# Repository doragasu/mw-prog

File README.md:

# WARNING: THIS PROJECT HAS MOVED

You can find the most recent version at the [mw-prog GitLab project page](https://gitlab.com/doragasu/mw-prog). This repository will be kept as is, and will not be updated anymore.

# mw-prog
MegaWiFi Programmer

This programmer is for the MegaWiFi project. It can write SEGA Genesis/Megadrive ROM files to MegaWiFi cartridges (up to 32 Mbit). It can also upload firmware blobs to the WiFi module inside MegaWiFi cartridges. To do so, you will need:

- Programmer bootloader: https://github.com/doragasu/mw-mdma-bl
- Programmer firmware: https://github.com/doragasu/mw-mdma-fw
- Programmer command-line interface: https://github.com/doragasu/mw-mdma-cli

And of course a both a MegaWiFi programmer and the target MegaWiFi cartridge.

This project was initially created for 1985alternativo, but to this day, no brave soul has dared to make an online game using this cart. Are you brave enough to try?

## License
mw-prog is licensed under the [CERN OHL 1.2](http://www.ohwr.org/licenses/cern-ohl/v1.2) license. You are free to study, distribute and make modifications to the Documentation, under the aforementioned license terms. You are also free to make cartridges derived from the Documentation for non-commercial purposes. If you want to make a commercial Product using this Documentation, please contact me to obtain a licence.

## About CAD files
Electronic CAD design files are for KiCAD Open Source electronics design suite. Please install latest version along with KiCAD libraries to open the project. When opening schematic, KiCAD will most likely complain about missing library "doragasu". Despite this warning, the schematic should load nicely (using the cached libraries). To avoid this message, install [the missing library](https://github.com/doragasu/doragasu-kicad-lib) and make sure to configure it in the schematic editor.

The files under `gerber` directory are for PCB fabrication. Send them to your favorite PCB fab house.

Files under `enclosure` directory are for the design and fabrication of the PCB enclosure. You can 3D-print the OBJ files to have a not specially pretty but functional enclosure for the programmer. If you want to edit the design files, you will need FreeCAD.

Enjoy!

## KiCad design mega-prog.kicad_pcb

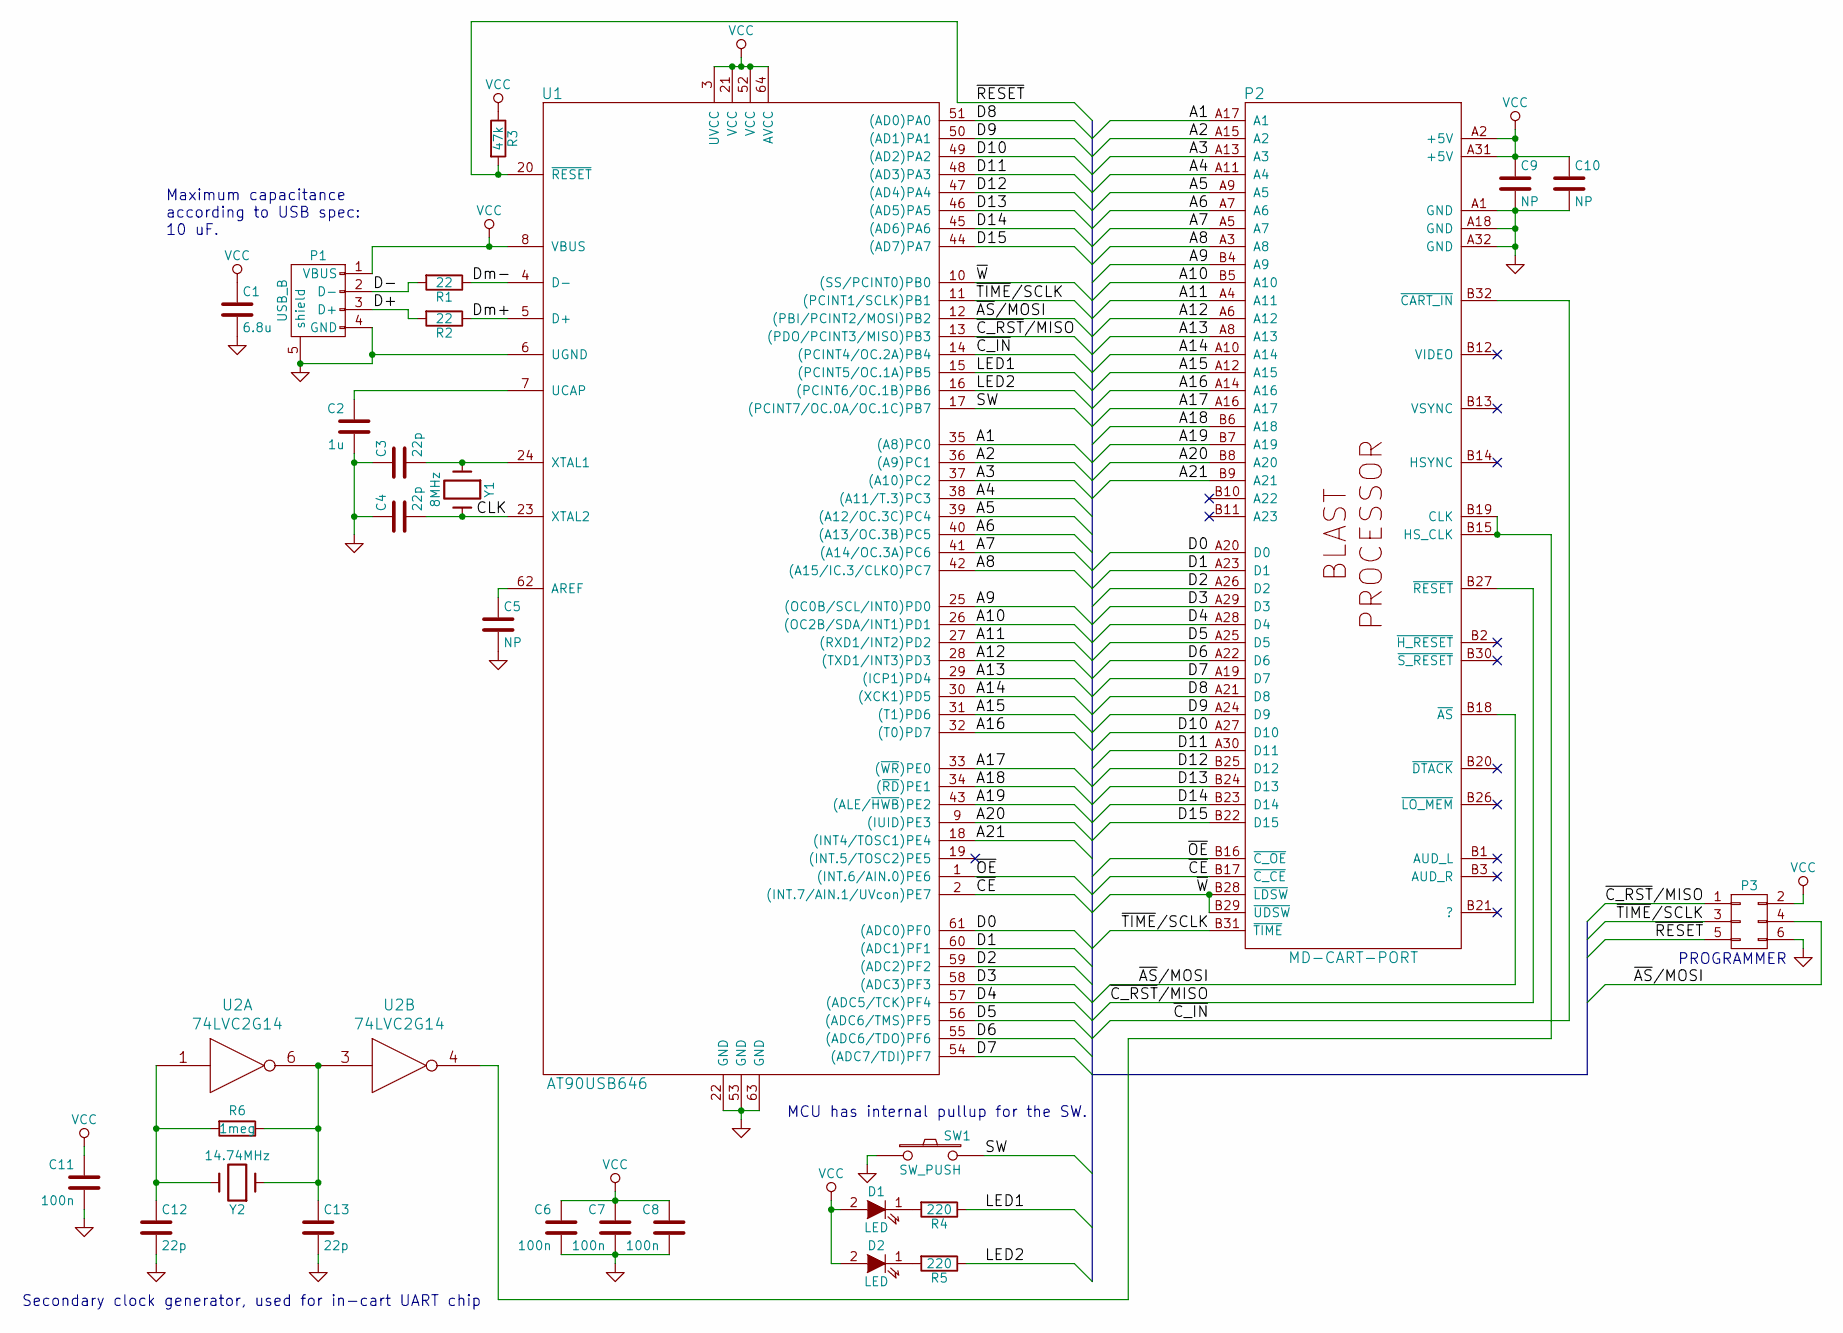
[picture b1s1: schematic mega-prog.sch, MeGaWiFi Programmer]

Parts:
C1: 6.8u; Capacitor5x11RM2.5
C2: 1u; C_0805
C3, C4, C12, C13: 22p; C_0805
C5, C9, C10: NP; C_0805
C6, C7, C8, C11: 100n; C_0805
D1, D2: LED; LED-5MM
P1: USB_B
P2: MD-CART-PORT; GEN_CART_PORT
P3: CONN_02X03; Pin_Header_Straight_2x03
R1, R2: 22; R_0805
R3: 47k; R_0805
R4, R5: 220; R_0805
R6: 1meg; R_0805
SW1: SW_PUSH; SW_PUSH_SMALL
U1: AT90USB646; LQFP-64_14x14mm_Pitch0.8mm
U2: 74LVC2G14; SOT23-6
Y1: 8MHz; Crystal_HC49-U_Vertical
Y2: 14.74MHz; Crystal_HC49-U_Vertical

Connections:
/A1: P2.A17 (A1), U1.35 ((A8)PC0)
/A2: P2.A15 (A2), U1.36 ((A9)PC1)
/A3: P2.A13 (A3), U1.37 ((A10)PC2)
/A4: P2.A11 (A4), U1.38 ((A11/T.3)PC3)
/A5: P2.A9 (A5), U1.39 ((A12/OC.3C)PC4)
/A6: P2.A7 (A6), U1.40 ((A13/OC.3B)PC5)
/A7: P2.A5 (A7), U1.41 ((A14/OC.3A)PC6)
/A8: P2.A3 (A8), U1.42 ((A15/IC.3/CLKO)PC7)
/A9: P2.B4 (A9), U1.25 ((OC0B/SCL/INT0)PD0)
/A10: P2.B5 (A10), U1.26 ((OC2B/SDA/INT1)PD1)
/A11: P2.A4 (A11), U1.27 ((RXD1/INT2)PD2)
/A12: P2.A6 (A12), U1.28 ((TXD1/INT3)PD3)
/A13: P2.A8 (A13), U1.29 ((ICP1)PD4)
/A14: P2.A10 (A14), U1.30 ((XCK1)PD5)
/A15: P2.A12 (A15), U1.31 ((T1)PD6)
/A16: P2.A14 (A16), U1.32 ((T0)PD7)
/A17: P2.A16 (A17), U1.33 ((~WR~)PE0)
/A18: P2.B6 (A18), U1.34 ((~RD~)PE1)
/A19: P2.B7 (A19), U1.43 ((ALE/~HWB~)PE2)
/A20: P2.B8 (A20), U1.9 ((IUID)PE3)
/A21: P2.B9 (A21), U1.18 ((INT4/TOSC1)PE4)
/CLK: C4.2, U1.23 (XTAL2), Y1.2
/D0: P2.A20 (D0), U1.61 ((ADC0)PF0)
/D1: P2.A23 (D1), U1.60 ((ADC1)PF1)
/D2: P2.A26 (D2), U1.59 ((ADC2)PF2)
/D3: P2.A29 (D3), U1.58 ((ADC3)PF3)
/D4: P2.A28 (D4), U1.57 ((ADC5/TCK)PF4)
/D5: P2.A25 (D5), U1.56 ((ADC6/TMS)PF5)
/D6: P2.A22 (D6), U1.55 ((ADC6/TDO)PF6)
/D7: P2.A19 (D7), U1.54 ((ADC7/TDI)PF7)
/D8: P2.A21 (D8), U1.51 ((AD0)PA0)
/D9: P2.A24 (D9), U1.50 ((AD1)PA1)
/D10: P2.A27 (D10), U1.49 ((AD2)PA2)
/D11: P2.A30 (D11), U1.48 ((AD3)PA3)
/D12: P2.B25 (D12), U1.47 ((AD4)PA4)
/D13: P2.B24 (D13), U1.46 ((AD5)PA5)
/D14: P2.B23 (D14), U1.45 ((AD6)PA6)
/D15: P2.B22 (D15), U1.44 ((AD7)PA7)
/D+: P1.3 (D+), R2.2
/D-: P1.2 (D-), R1.2
/Dm+: R2.1, U1.5 (D+)
/Dm-: R1.1, U1.4 (D-)
/LED1: R4.1, U1.15 ((PCINT5/OC.1A)PB5)
/LED2: R5.1, U1.16 ((PCINT6/OC.1B)PB6)
/SW: SW1.2, U1.17 ((PCINT7/OC.0A/OC.1C)PB7)
/~AS~/MOSI: P2.B18 (~AS), P3.4, U1.12 ((PBI/PCINT2/MOSI)PB2)
/~CE: P2.B17 (~C_CE), U1.2 ((INT.7/AIN.1/UVcon)PE7)
/~C_IN: P2.B32 (~CART_IN), U1.14 ((PCINT4/OC.2A)PB4)
/~C_RST~/MISO: P2.B27 (~RESET), P3.1, U1.13 ((PDO/PCINT3/MISO)PB3)
/~OE: P2.B16 (~C_OE), U1.1 ((INT.6/AIN.0)PE6)
/~RESET: P3.5, R3.2, U1.20 (~RESET)
/~TIME~/SCLK: P2.B31 (~TIME), P3.3, U1.11 ((PCINT1/SCLK)PB1)
/~W: P2.B28 (~LDSW), P2.B29 (~UDSW), U1.10 ((SS/PCINT0)PB0)
GND: C1.2, C2.2, C3.1, C4.1, C5.2, C6.2, C7.2, C8.2, C9.2, C10.2, C11.2, C12.2, C13.2, P1.4 (GND), P1.5 (shield), P2.A1 (GND), P2.A18 (GND), P2.A32 (GND), P3.6, SW1.1, U1.6 (UGND), U1.22 (GND), U1.53 (GND), U1.63 (GND), U2.2 (GND)
unnamed: C2.1, U1.7 (UCAP)
unnamed: C3.2, U1.24 (XTAL1), Y1.1
unnamed: C5.1, U1.62 (AREF)
unnamed: C12.1, R6.2, U2.1, Y2.2
unnamed: C13.1, R6.1, U2.3, U2.6, Y2.1
unnamed: D1.1 (K), R4.2
unnamed: D2.1 (K), R5.2
unnamed: P2.B15 (HS_CLK), P2.B19 (CLK), U2.4
VCC: C1.1, C6.1, C7.1, C8.1, C9.1, C10.1, C11.1, D1.2 (A), D2.2 (A), P1.1 (VBUS), P2.A2 (+5V), P2.A31 (+5V), P3.2, R3.1, U1.3 (UVCC), U1.8 (VBUS), U1.21 (VCC), U1.52 (VCC), U1.64 (AVCC), U2.5 (VCC)

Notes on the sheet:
MCU has internal pullup for the SW.
Maximum capacitance according to USB spec: 10 uF.
PROGRAMMER
Secondary clock generator, used for in-cart UART chip

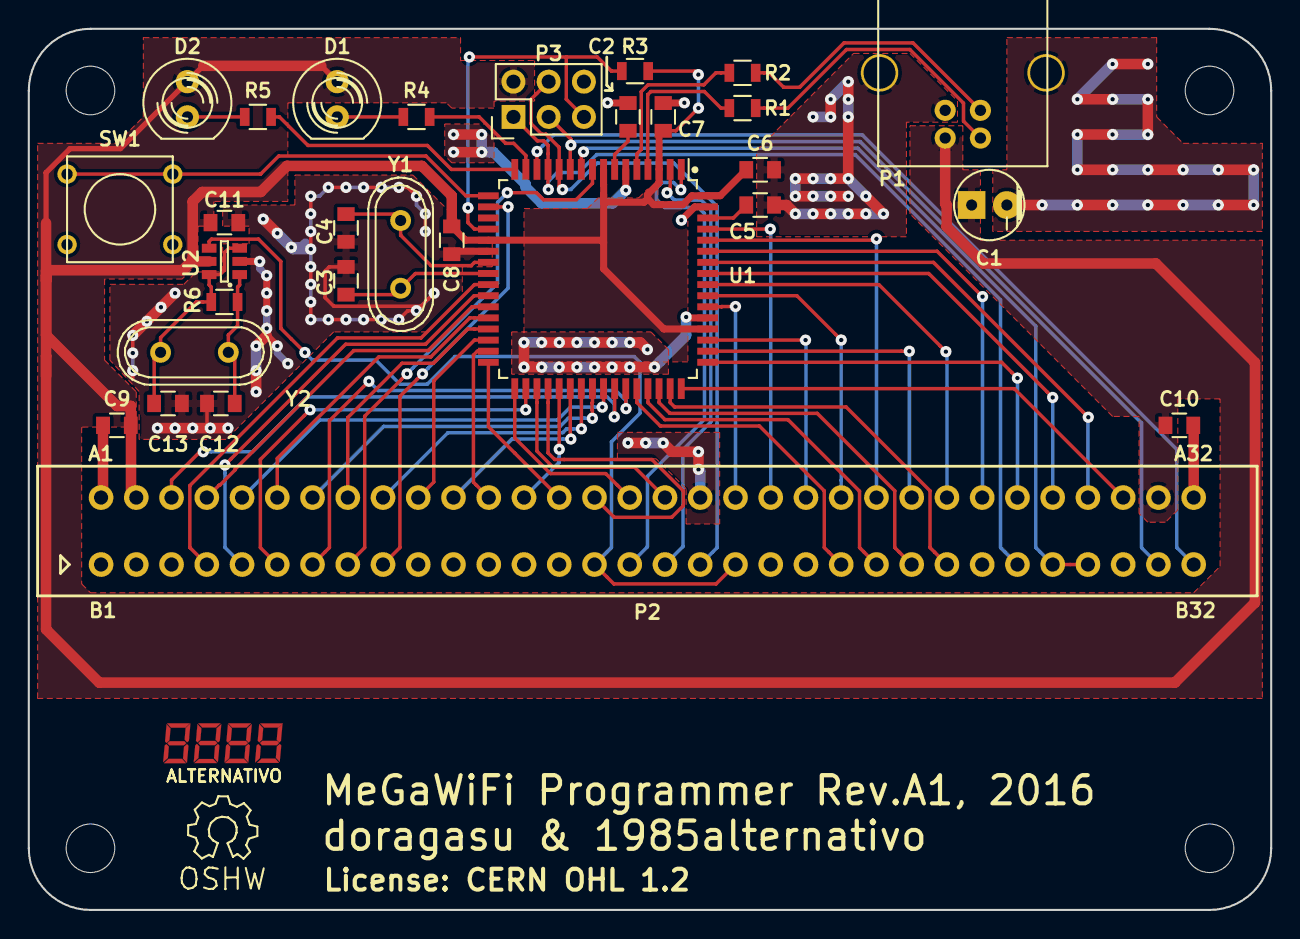
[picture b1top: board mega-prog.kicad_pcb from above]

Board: 2 copper layers, 89.5 x 63.5 mm, 34 parts (0 on the bottom side), 63 nets.

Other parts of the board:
MountingHole_3-5mm, MountingHole_3-5mm#2, MountingHole_3-5mm#3, MountingHole_3-5mm#4: VAL**; MountingHole_3-5mm
Symbol_OSHW-Logo_SilkScreen: VAL**; Symbol_OSHW-Logo_SilkScreen

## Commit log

2017-03-24 Added design files.
2017-09-24 BOM changes.
2018-04-07 Updated to latest KiCad and libraries version.

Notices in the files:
mega-prog.kicad_pcb:
License: not yet decided
License: CERN OHL 1.2
